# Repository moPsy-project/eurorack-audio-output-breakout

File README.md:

# moPsyOct breakOUT

> Breakout board for Eurorack Power Output on the breadboard

* Unity-Gain OpAmp circuit to bring audio from your Breadboard to the synthesizer
* Attach your patch cables hassle-free
* Uses THT for easy assembly

## Dependencies

This project uses symbols from the [moPsy-KiCad-resources](https://github.com/moPsy-project/moPsy-KiCad-resources).

## License

This work is licensed under a [Creative Commons Attribution-ShareAlike 4.0 International License](http://creativecommons.org/licenses/by-sa/4.0/).

BY: Stefan Haun (mail@tuxathome.de)

See [LICENSE.txt](LICENSE.txt) for details.

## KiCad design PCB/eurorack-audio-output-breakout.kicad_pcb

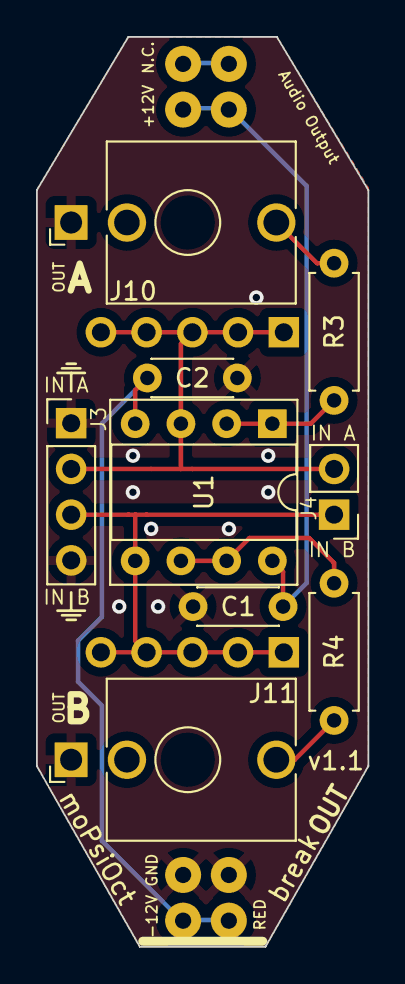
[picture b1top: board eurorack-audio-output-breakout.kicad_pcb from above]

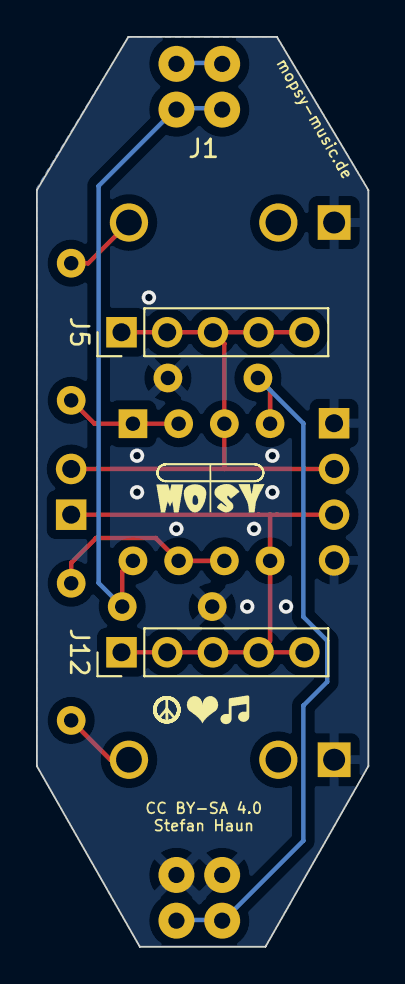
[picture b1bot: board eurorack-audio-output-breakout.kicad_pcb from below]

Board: 2 copper layers, 18.4 x 50.5 mm, 12 parts (3 on the bottom side), 9 nets.

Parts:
C1, C2: 100n; C_Disc_D4.3mm_W1.9mm_P5.00mm
J1: Conn_01x04_Pin; Breadboard Power Connector
J3: Conn_01x04_Pin; PinHeader_1x04_P2.54mm_Vertical
J4: Conn_01x02_Pin; PinHeader_1x02_P2.54mm_Vertical
J5, J12: Conn_01x05_Pin; PinHeader_1x05_P2.54mm_Vertical
J10: A; Jack_3.5mm_QingPu_WQP-PJ398SM_Vertical_CircularHoles_Center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
J11: B; Jack_3.5mm_QingPu_WQP-PJ398SM_Vertical_CircularHoles_Center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
R3, R4: 1k; R_Axial_DIN0207_L6.3mm_D2.5mm_P7.62mm_Horizontal
U1: TL072; DIP-8_W7.62mm_Socket

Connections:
+12V: C1.1, J1.2, U1.8 (V+)
-12V: C2.2, J1.4, U1.4 (V-)
GND: C1.2, C2.1, J1.3, J3.1, J3.4, J10.S, J11.S
unnamed: J3.2, J4.2, J5.1, J5.2, J5.3, J5.4, J5.5, U1.3 (+)
unnamed: J10.T, R3.2
unnamed: J11.T, R4.2
unnamed: J3.3, J4.1, J12.1, J12.2, J12.3, J12.4, J12.5, U1.5 (+)
unnamed: R3.1, U1.1, U1.2 (-)
unnamed: R4.1, U1.6 (-), U1.7

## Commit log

2023-11-23 Add sponsorship information
2023-11-23 Add release workflow
2023-11-23 Add gitignore for KiCad project
2023-11-23 First PCB draft
2023-11-23 Make the design slimmer
2023-11-23 Remove some components and make PCB slimmer
    Reverse protection and pull-down are not really needed in a
    breadboard environment, as component placement needs care and
    focus anyways. Remove these components and make the PCB slimmer.
2023-11-23 Adapt README to changed features
2023-11-25 Change spelling of "moPsiOct"
2023-11-25 Add A/B designators to the two channels
2023-11-26 Use part for breadboard power and fix spacing
2023-11-26 Fix U1 footprint
2024-05-09 Adjust for new KiCad version
2024-08-21 Fix header and text placement
2024-08-21 Fix placement, again
2024-08-21 Fix placement with reference

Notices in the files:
PCB/eurorack-audio-output-breakout.kicad_pcb:
CC BY-SA 4.0
